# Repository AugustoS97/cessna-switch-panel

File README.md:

# cessna-switch-panel

## Descripción

Panel para interruptores de luces y magnetos para Cessna 172 y otros simuladores de vuelo. Diseñado para ser compatible con MobiFlight y FSX, MSFS2020, Xplane y Prepar3D.

## Contenido del proyecto

- En la carpeta cessna-panel-pcb se incluye el diseño de PCB para ser controlado con un arduino Mega 2560 Pro, con los ficheros GERBER para ser pedido en JLCPCB.
- En la carpeta Frame-design se localizan los diseños 3D de los marcos para los interruptores tanto para instalación vertical como horizontal.
- En la carpeta PCB-Support se localizan los diseños 3D de la carcasa para la electrónica.
- En la carpeta Mobiflight Confif se localiza el fichero de configuración d eMobiflight para Cessna 172 y MSFS2020.

Enlace del diseño de [paneles](https://www.thingiverse.com/thing:5461243) y [carcasa](https://www.thingiverse.com/thing:5461228) en Thingiverse.

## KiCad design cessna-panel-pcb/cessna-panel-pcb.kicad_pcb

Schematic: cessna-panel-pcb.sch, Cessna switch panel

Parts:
C1, C2, C3, C4, C5, C6, C7, C8, C9, C10, C11, C12, C13, C14, C15: 10nF; C_Disc_D3.8mm_W2.6mm_P2.50mm
J1, J2, J3, J4, J5, J6, J7, J16, J21, J22, J23, J24, J25, J26: Screw_Terminal_01x02; TerminalBlock_bornier-2_P5.08mm
J8: PWM1_CONN; PinSocket_1x03_P2.54mm_Vertical
J9: PWM2_CONN; PinSocket_1x03_P2.54mm_Vertical
J10: PWM3_CONN; PinSocket_1x03_P2.54mm_Vertical
J11: PWM4_CONN; PinSocket_1x03_P2.54mm_Vertical
J12: PWM5_CONN; PinSocket_1x03_P2.54mm_Vertical
J13: PWM6_CONN; PinSocket_1x03_P2.54mm_Vertical
J14: PWM7_CONN; PinSocket_1x03_P2.54mm_Vertical
J15: PWM8_CONN; PinSocket_1x03_P2.54mm_Vertical
J17: PWM9_CONN; PinSocket_1x03_P2.54mm_Vertical
J18: PWM10_CONN; PinSocket_1x03_P2.54mm_Vertical
J19: PWM11_CONN; PinSocket_1x03_P2.54mm_Vertical
J20: PWM12_CONN; PinSocket_1x03_P2.54mm_Vertical
MCU1: Master_Arduino_Mega_Embebido_Arduino_Mega_v3; MEGA_Embebido

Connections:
+5V: J7.1, J8.2, J9.2, J10.2, J11.2, J12.2, J13.2, J14.2, J15.2, J17.2, J18.2, J19.2, J20.2, MCU1.5, MCU1.6
BCN: C4.1, J4.1, MCU1.26
BOTH_MAGN: C14.1, J25.2, MCU1.38
FUEL_PUMP: C2.1, J2.1, MCU1.25
GND: C1.2, C2.2, C3.2, C4.2, C5.2, C6.2, C7.2, C8.2, C9.2, C10.2, C11.2, C12.2, C13.2, C14.2, C15.2, J1.2, J2.2, J3.2, J4.2, J5.2, J6.2, J7.2, J8.3, J9.3, J10.3, J11.3, J12.3, J13.3, J14.3, J15.3, J16.2, J17.3, J18.3, J19.3, J20.3, J21.2, J22.2, J23.2, J26.2, MCU1.3, MCU1.4
LAND: C6.1, J6.1, MCU1.27
L_MAGN: C13.1, J24.1, MCU1.37
MASTER_ALT: C1.1, J1.1, MCU1.32
MASTER_AVIONIC: C5.1, J5.1, MCU1.34
MASTER_BAT: C3.1, J3.1, MCU1.33
NAV: C8.1, J21.1, MCU1.29
OFF_MAGN: C11.1, J23.1, MCU1.35
PITOT_HEAT: C15.1, J26.1, MCU1.31
PWM1: J8.1, MCU1.13
PWM2: J9.1, MCU1.14
PWM3: J10.1, MCU1.15
PWM4: J11.1, MCU1.16
PWM5: J12.1, MCU1.17
PWM6: J13.1, MCU1.18
PWM7: J14.1, MCU1.19
PWM8: J15.1, MCU1.20
PWM9: J17.1, MCU1.21
PWM10: J18.1, MCU1.22
PWM11: J19.1, MCU1.23
PWM12: J20.1, MCU1.24
R_MAGN: C12.1, J24.2, MCU1.36
START_MAGN: C10.1, J25.1, MCU1.39
STROBE: C9.1, J22.1, MCU1.30
TAXI: C7.1, J16.1, MCU1.28

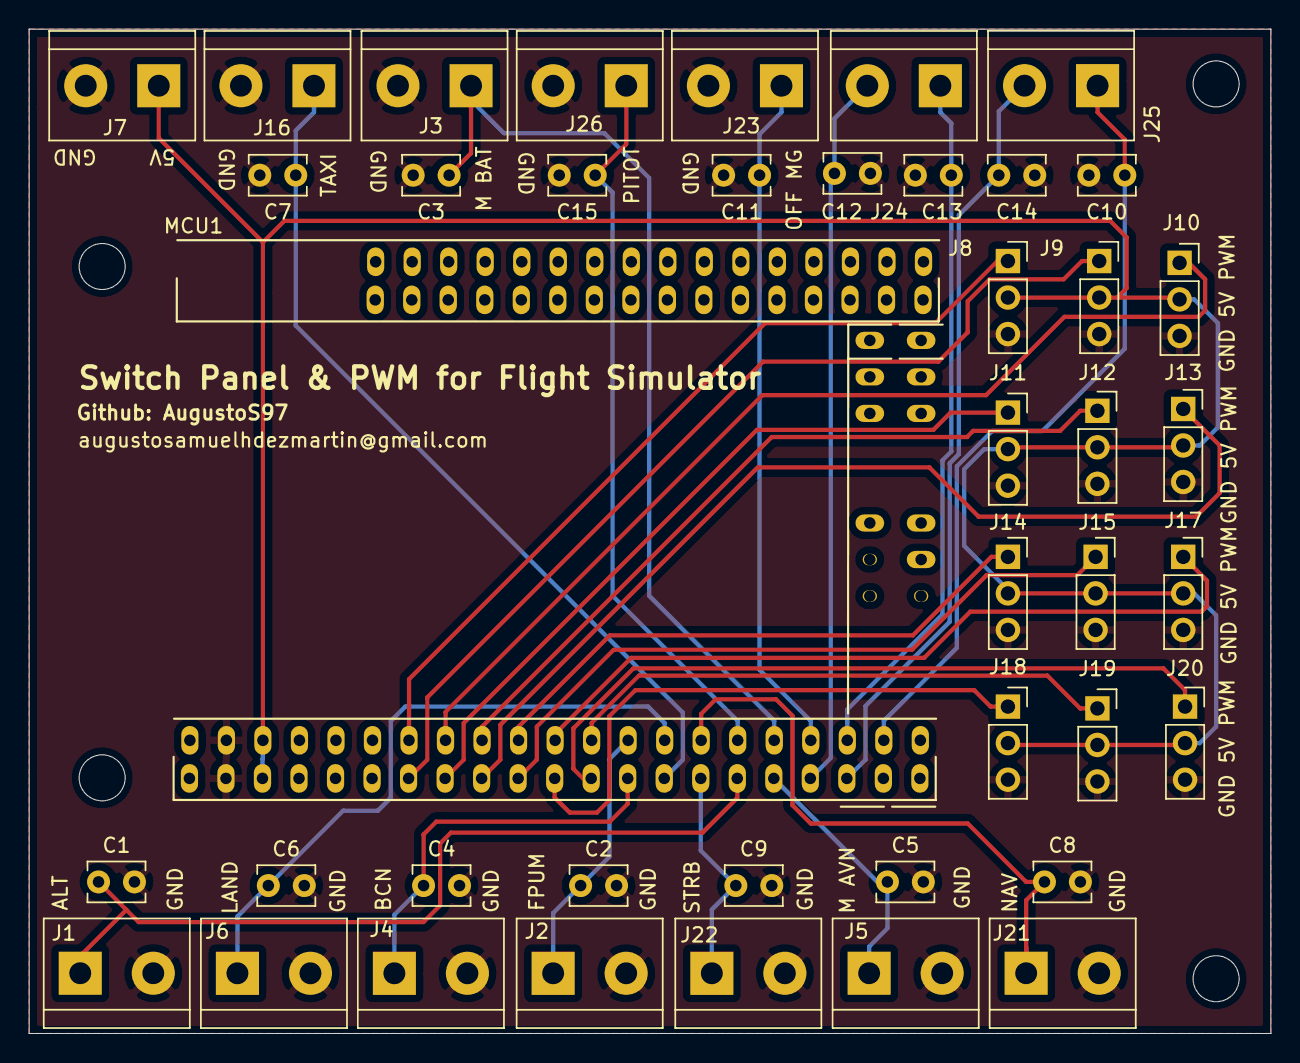
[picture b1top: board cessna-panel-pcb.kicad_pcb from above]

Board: 2 copper layers, 86.4 x 69.9 mm, 46 parts (0 on the bottom side), 29 nets.

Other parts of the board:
H1, H2, H3, H4: MountingHole_3.2mm_M3

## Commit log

2021-09-19 Añadido el esquematico. Falta la PCB.
2021-10-03 Diseño de PCb para conectar los Switches y los servos diseñada.
2021-10-10 Modificados los GERBERs
2021-10-11 Añadido el diseño del panel y sus ficheros imprimibles.
2021-10-12 Corregidas las dimensiones de los rocket switch
2022-08-14 Añadidos los diseños de carcasas, el modelo 3D de PCB y los ficheros Fusion 360
